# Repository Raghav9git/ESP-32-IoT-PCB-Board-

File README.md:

## ESP32-C3 IoT Sensor Development Board

A compact 4-layer IoT development board built around the ESP32-C3, integrating environmental sensing, local storage, USB-C power with LiPo battery management, and a programming/debug interface on a single board. Designed in KiCad 10.0.

This is a multi-domain hardware project that brings power electronics, mixed-signal sensor front-ends, digital interfaces, and RF-module integration together on one board — and routes them on a 4-layer stackup with dedicated power and ground planes.

## Overview

The goal of this board is a self-contained, battery-capable IoT platform: an ESP32-C3 (Wi-Fi + BLE) as the brain, surrounded by the supporting subsystems a real IoT device needs — clean regulated power, safe battery charging, local data storage, environmental sensors, and a robust USB programming path.

It was built as a deliberate skill-development project to practice end-to-end PCB design across several engineering domains in a single, non-trivial board, rather than a series of isolated single-function boards.

## Features

MCU: ESP32-C3-WROOM-02 module — Wi-Fi + Bluetooth LE
Power input: USB-C connector (power + data), with input fuse protection
Battery: LiPo battery connector with onboard charge management (MCP73871) and power-path control
Regulation: 3.3 V LDO (LM1117) for the logic rail, sourced from the 5 V USB rail
Programming/Debug: CP2102N USB-to-UART bridge with automatic boot/reset (DTR/RTS) circuit
Storage: microSD card slot (SPI) + onboard SPI flash (W25Q32)
Sensors:

BME280 — temperature, humidity, barometric pressure
TEMT6000 — ambient light
Electret microphone + MAX4466 pre-amplifier — audio/sound level

User interface: Boot and Reset buttons (with RC debounce), status LEDs, I²C OLED display header, GPIO breakout header
Debug: Test points on key SPI/SD signals
Protection: USB data-line ESD protection (USBLC6)
PCB: 4-layer design with dedicated power and ground planes

## Tech Specs

ItemDetailMicrocontrollerESP32-C3-WROOM-02 (Wi-Fi + BLE)PCB layers4 (signal / GND plane / power plane / signal)Power inputUSB-C (5 V) and LiPo batteryLogic rail3.3 V (LM1117 LDO)ChargingMCP73871 LiPo charger / power pathUSB–UART bridgeCP2102NStoragemicroSD (SPI) + W25Q32 SPI flashSensorsBME280, TEMT6000, MAX4466 mic ampInterfacesI²C, SPI, UART, GPIO headerDesign toolKiCad 10.0

## Subsystem Architecture

The board is organized as a set of interacting subsystems. Each block exists for a specific reason:

## Power & Battery Management

USB-C delivers 5 V, passed through a fuse for input protection. The MCP73871 handles LiPo charging and automatic power-path switching between USB power and battery, so the board runs from USB when connected and from battery otherwise. The LM1117 LDO derives the clean 3.3 V logic rail from the 5 V rail. Input and output decoupling capacitors sit close to the regulator for stability.

## MCU

The ESP32-C3-WROOM-02 is the core — a single-chip Wi-Fi + BLE module. It runs from the 3.3 V rail with local decoupling, and exposes the SPI, I²C, UART, and GPIO interfaces that connect to the rest of the board.

## Programming & Auto-Reset

A CP2102N USB-to-UART bridge provides the serial programming/debug interface over USB-C. The DTR/RTS auto-reset circuit (two transistors) automatically drives the EN and BOOT lines during flashing, so firmware can be uploaded without manually pressing buttons — the standard ESP programming convenience circuit. USBLC6 ESD protection guards the USB data lines.

## Storage

A microSD slot (SPI) provides removable local storage for data logging, and an onboard W25Q32 SPI flash offers fixed storage for configuration or firmware data. Test points on the SPI/SD lines allow probing during bring-up.

## Sensors (Mixed-Signal Front-Ends)

BME280 — digital environmental sensor (temperature, humidity, pressure) on the I²C/SPI bus.
TEMT6000 — analog ambient light sensor feeding an ADC input.
Electret mic + MAX4466 — an analog audio front-end; the MAX4466 amplifies the microphone signal to a usable level for the ADC.

The analog sensor front-ends are the mixed-signal portion of the design, where layout and grounding affect signal quality.

## User Interface

Boot and Reset buttons with RC debounce, status LEDs for power/operation indication, an I²C header for an OLED display, and a GPIO breakout header for expansion.

## Design Highlights

4-layer stackup with dedicated ground and power planes for clean power distribution and a solid low-impedance ground return — important on a board mixing RF, analog sensors, and digital interfaces.
Mixed-signal layout — separating noisy digital and switching activity from the analog sensor front-ends.
USB & ESD considerations — controlled USB data routing and dedicated ESD protection.
Net classes for differentiated trace widths (power vs. signal).
Test points on key debug nets for hardware bring-up.
Compact, thoughtful component placement following the power and signal flow.

## Project Status

~80% complete.

 Multi-page hierarchical schematic — complete, ERC passing
 Footprint assignment
 Component placement
 4-layer stackup and plane setup
 Routing (power and signal)
 Copper zones / ground pour
 Final silkscreen pass (labels, polarity marks, board info)
 Final DRC sign-off
 Manufacturing output (Gerbers / drill files)
 Fabrication and bring-up testing

Remaining work is finishing/polish: silkscreen cleanup, a final DRC pass, and generating manufacturing files.

## Skills Developed

This project was built to practice the full PCB workflow on a realistic, multi-domain board:

Multi-page hierarchical schematic design
Power electronics: LDO regulation, LiPo charge management, power-path design
Mixed-signal design: analog sensor front-ends alongside digital interfaces
RF module integration: ESP32-C3 placement and supporting circuitry
Digital interfaces: SPI (flash, SD), I²C (sensors, OLED), UART (programming)
USB & ESD: USB-C, USB-to-UART bridge, data-line protection
4-layer PCB layout: stackup, dedicated power/ground planes, copper zones
Net classes, trace-width selection, and DRC-driven debugging
Reading and applying datasheets for component configuration

## Tools

KiCad 10.0 — schematic capture and PCB layout
Component symbols, footprints, and 3D models sourced from KiCad libraries and standard component vendors

## References & Acknowledgments

This board was built as a learning project to develop hands-on PCB design skills across power, mixed-signal, and digital domains. The design follows and adapts a published KiCad IoT development-board reference/tutorial as a starting point, which I used to study how a complete, multi-subsystem board is architected, laid out on four layers, and prepared for manufacturing.

License

Released under the MIT License. See LICENSE for details.

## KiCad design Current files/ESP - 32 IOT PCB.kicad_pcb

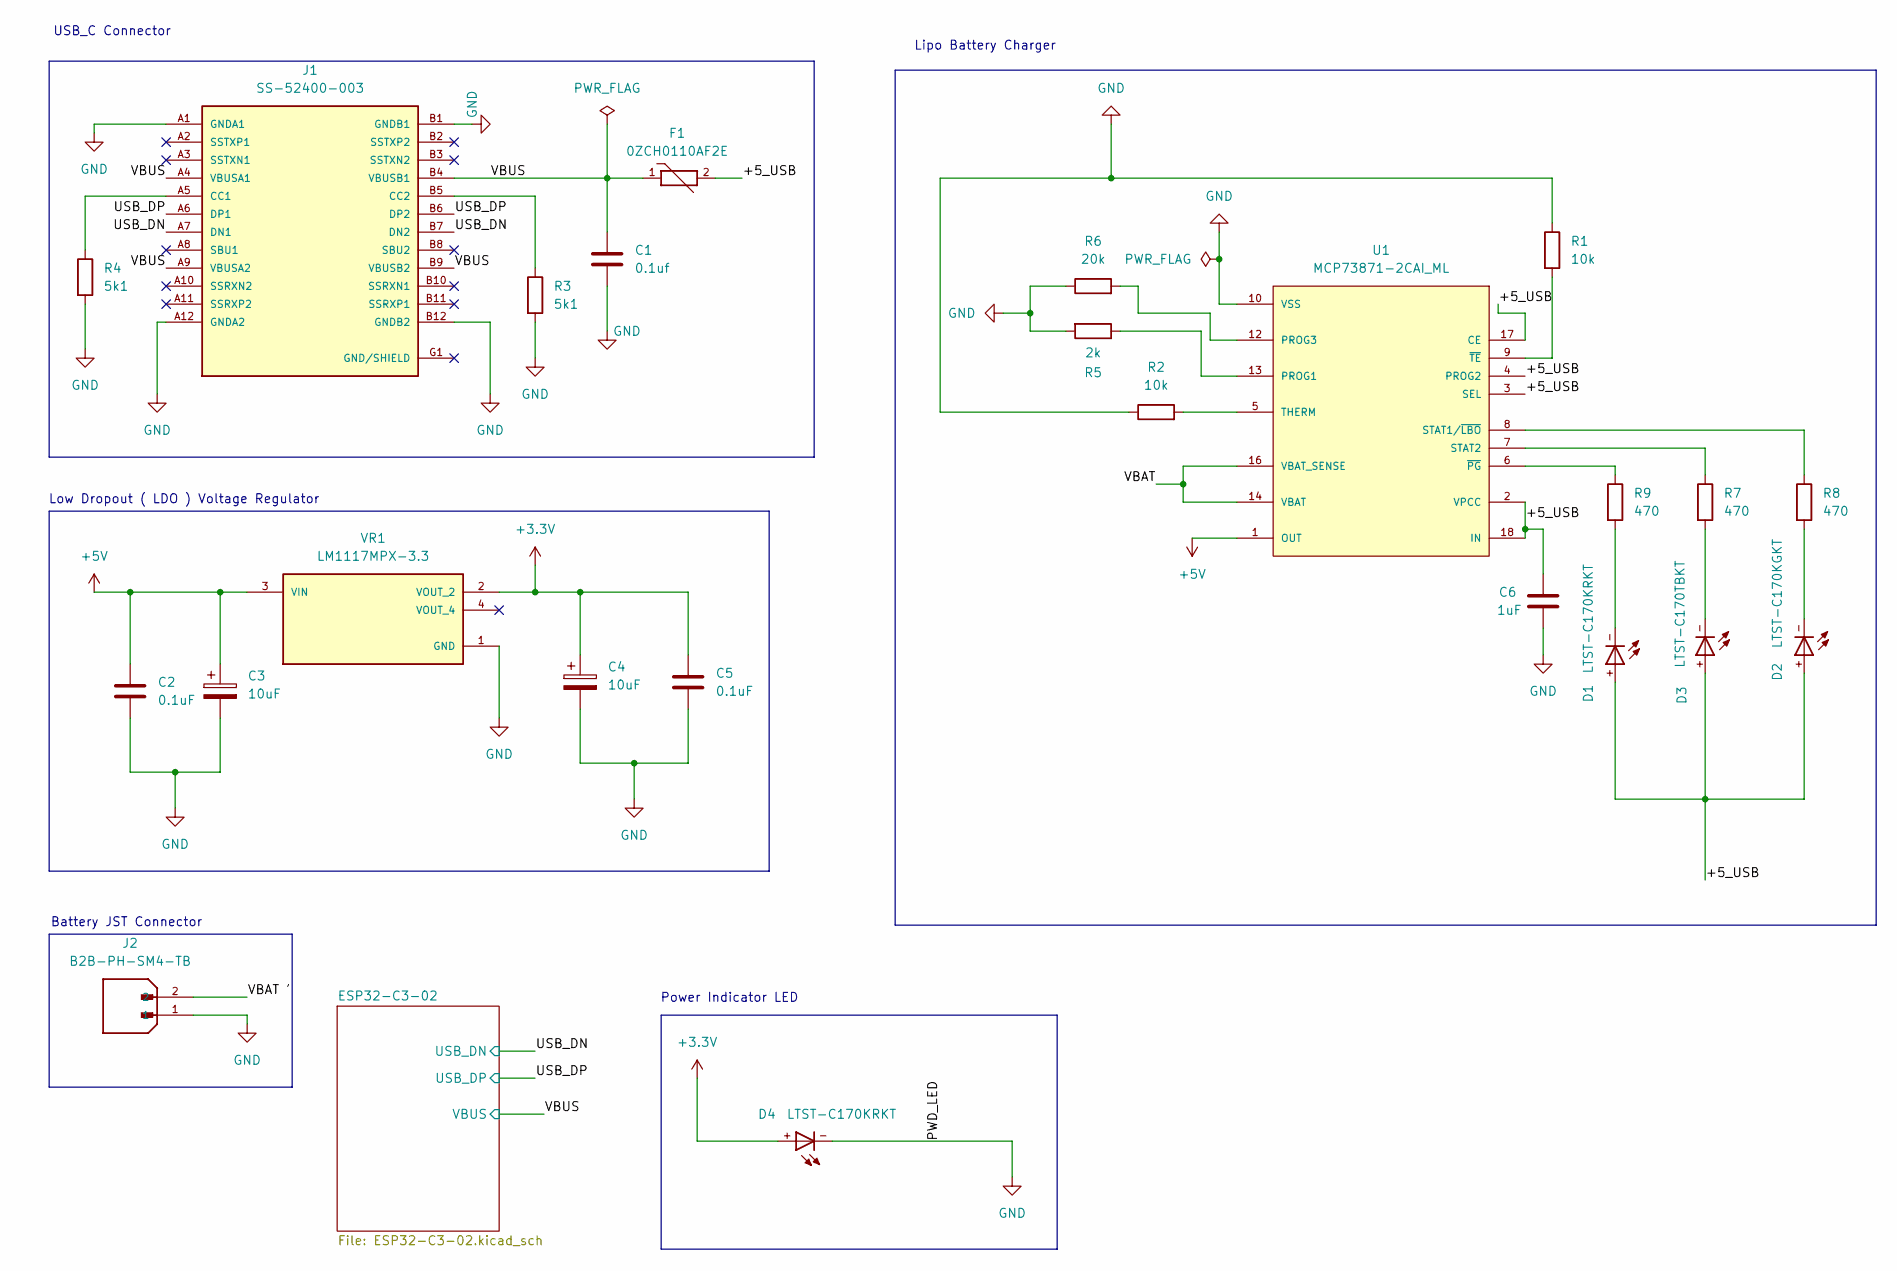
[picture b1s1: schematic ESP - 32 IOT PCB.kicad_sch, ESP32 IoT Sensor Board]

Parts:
C1: 0.1uf; C_0805_2012Metric
C2, C5: 0.1uF; C_0805_2012Metric
C3, C4: 10uF; CP_EIA-3216-18_Kemet-A
C6: 1uF; C_0805_2012Metric
D1, D4: LTST-C170KRKT; DIOC200X125X110
D2: LTST-C170KGKT; DIOC200X125X110
D3: LTST-C170TBKT; DIOC200X125X110
F1: 0ZCH0110AF2E; FUSC3225X100N; PARTREV Apr2023
J1: SS-52400-003; BELFUSE_SS-52400-003; PARTREV A0
J2: B2B-PH-SM4-TB; JST_B2B-PH-SM4-TB; PARTREV N/A
R1, R2: 10k; R_0805_2012Metric
R3, R4: 5k1; R_0805_2012Metric
R5: 2k; R_0805_2012Metric
R6: 20k; R_0805_2012Metric
R7, R8, R9: 470; R_0805_2012Metric
U1: MCP73871-2CAI_ML; QFN50P400X400X100-21N; PARTREV D
VR1: LM1117MPX-3.3; VREG_LM1117MPX-3.3; PARTREV O

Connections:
+3.3V: C4.1, C5.1, D4.+, VR1.2 (VOUT_2); also elsewhere on the board
+5V: C2.1, C3.1, U1.1 (OUT), U1.20 (OUT), VR1.3 (VIN)
/+5_USB: C6.1, D1.+, D2.+, D3.+, F1.2, U1.2 (VPCC), U1.3 (SEL), U1.4 (PROG2), U1.17 (CE), U1.18 (IN), U1.19 (IN)
/USB_DN: J1.A7 (DN1), J1.B7 (DN2); also elsewhere on the board
/USB_DP: J1.A6 (DP1), J1.B6 (DP2); also elsewhere on the board
/VBAT: U1.14 (VBAT), U1.15 (VBAT), U1.16 (VBAT_SENSE)
/VBAT ': J2.2
/VBUS: C1.1, F1.1, J1.A4 (VBUSA1), J1.A9 (VBUSA2), J1.B4 (VBUSB1), J1.B9 (VBUSB2); also elsewhere on the board
GND: C1.2, C2.2, C3.2, C4.2, C5.2, C6.2, D4.-, J1.A1 (GNDA1), J1.A12 (GNDA2), J1.B1 (GNDB1), J1.B12 (GNDB2), J2.1, R1.1, R2.1, R3.2, R4.2, R5.2, R6.1, U1.10 (VSS), U1.11 (VSS), U1.21 (VSS), VR1.1 (GND); also elsewhere on the board
unnamed: D1.-, R9.2
unnamed: D2.-, R8.2
unnamed: D3.-, R7.2
unnamed: J1.A5 (CC1), R4.1
unnamed: J1.B5 (CC2), R3.1
unnamed: R5.1, U1.13 (PROG1)
unnamed: R6.2, U1.12 (PROG3)
unnamed: R8.1, U1.8 (STAT1/~LBO)
unnamed: R7.1, U1.7 (STAT2)
unnamed: R2.2, U1.5 (THERM)
unnamed: R9.1, U1.6 (~PG)
unnamed: R1.2, U1.9 (~TE)

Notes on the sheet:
Lipo Battery Charger
Power Indicator LED
USB_C Connector
Battery JST Connector
Low Dropout ( LDO ) Voltage Regulator

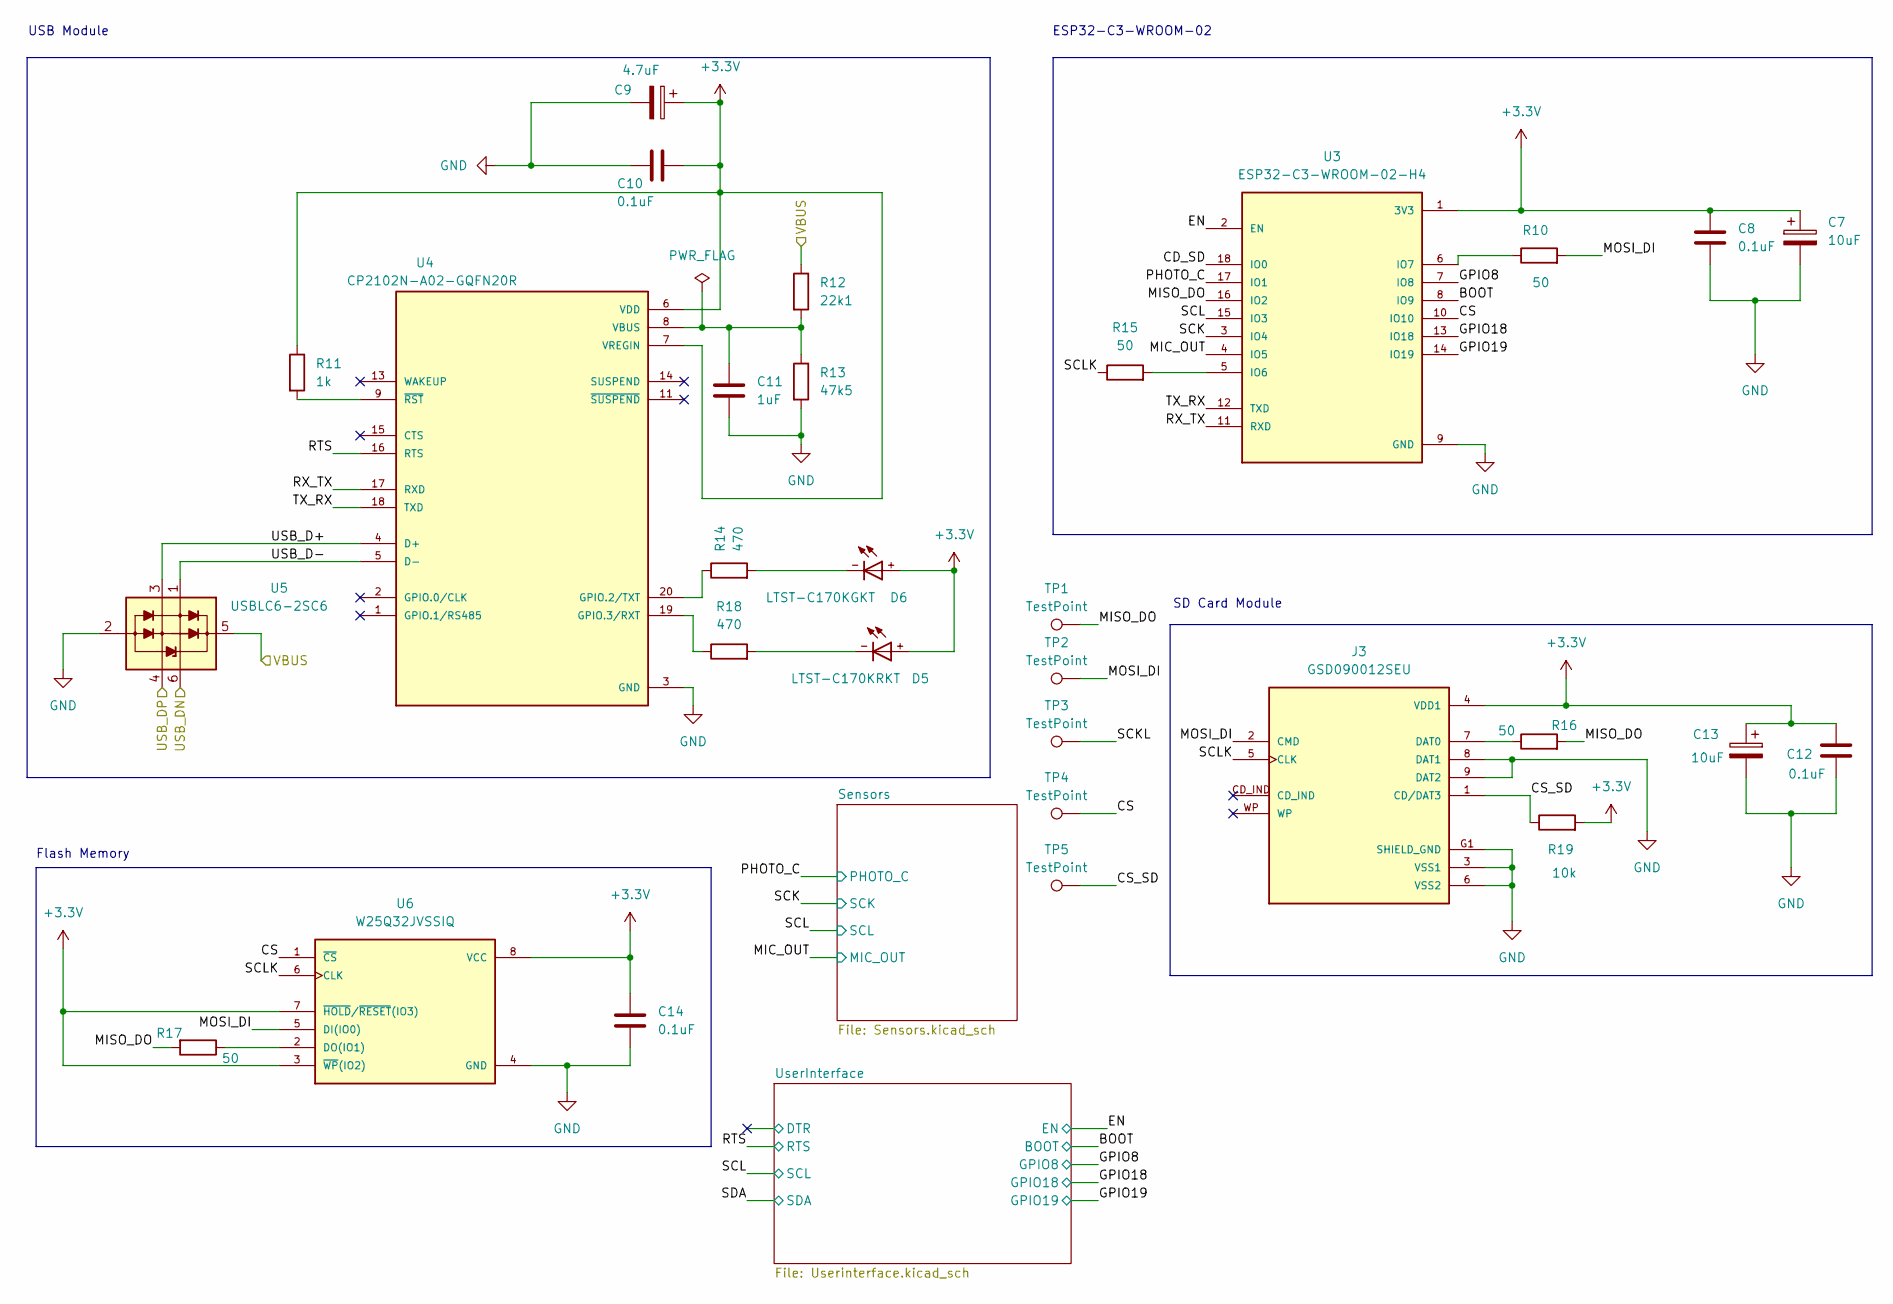
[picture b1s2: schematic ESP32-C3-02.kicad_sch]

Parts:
C7, C13: 10uF; CP_EIA-3216-18_Kemet-A
C8, C10, C12, C14: 0.1uF; C_0805_2012Metric
C9: 4.7uF; CP_EIA-3216-18_Kemet-A
C11: 1uF; C_0805_2012Metric
D5: LTST-C170KRKT; DIOC200X125X110
D6: LTST-C170KGKT; DIOC200X125X110
J3: GSD090012SEU; AMPHENOL_GSD090012SEU; PARTREV E
R10, R15, R16, R17: 50; R_0805_2012Metric
R11: 1k; R_0805_2012Metric
R12: 22k1; R_0805_2012Metric
R13: 47k5; R_0805_2012Metric
R14, R18: 470; R_0805_2012Metric
R19: 10k; R_0805_2012Metric
TP1, TP2, TP3, TP4, TP5: TestPoint; TestPoint_Pad_D1.0mm
U3: ESP32-C3-WROOM-02-H4; MODULE_ESP32-C3-WROOM-02-H4
U4: CP2102N-A02-GQFN20R; SILABS_CP2102N-A02-GQFN20R; PARTREV 1.3
U5: USBLC6-2SC6; SOT-23-6
U6: W25Q32JVSSIQ; SOIC127P790X216-8N; M_PART_NUMBER W25QXX

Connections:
+3.3V: C7.1, C8.1, C9.1, C10.2, C12.1, C13.1, C14.1, D5.+, D6.+, J3.4 (VDD1), R11.1, R19.2, U3.1 (3V3), U4.6 (VDD), U4.7 (VREGIN), U6.3 (~WP(IO2)), U6.7 (~HOLD/~RESET(IO3)), U6.8 (VCC); also elsewhere on the board
/ESP32-C3-02/BOOT: U3.8 (IO9); also elsewhere on the board
/ESP32-C3-02/CD_SD: U3.18 (IO0)
/ESP32-C3-02/CS: TP4.1, U3.10 (IO10), U6.1 (~CS)
/ESP32-C3-02/CS_SD: J3.1 (CD/DAT3), R19.1, TP5.1
/ESP32-C3-02/EN: U3.2 (EN); also elsewhere on the board
/ESP32-C3-02/GPIO8: U3.7 (IO8); also elsewhere on the board
/ESP32-C3-02/GPIO18: U3.13 (IO18); also elsewhere on the board
/ESP32-C3-02/GPIO19: U3.14 (IO19); also elsewhere on the board
/ESP32-C3-02/MIC_OUT: U3.4 (IO5); also elsewhere on the board
/ESP32-C3-02/MISO_DO: R16.2, R17.2, TP1.1, U3.16 (IO2)
/ESP32-C3-02/MOSI_DI: J3.2 (CMD), R10.2, TP2.1, U6.5 (DI(IO0))
/ESP32-C3-02/PHOTO_C: U3.17 (IO1); also elsewhere on the board
/ESP32-C3-02/RTS: U4.16 (RTS); also elsewhere on the board
/ESP32-C3-02/RX_TX: U3.11 (RXD), U4.17 (RXD)
/ESP32-C3-02/SCK: U3.3 (IO4); also elsewhere on the board
/ESP32-C3-02/SCL: U3.15 (IO3); also elsewhere on the board
/ESP32-C3-02/SCLK: J3.5 (CLK), R15.1, U6.6 (CLK)
/ESP32-C3-02/TX_RX: U3.12 (TXD), U4.18 (TXD)
/ESP32-C3-02/USB_D+: U4.4 (D+), U5.3 (L2)
/ESP32-C3-02/USB_D-: U4.5 (D-), U5.1 (L1)
/USB_DN: U5.6 (L1); also elsewhere on the board
/USB_DP: U5.4 (L2); also elsewhere on the board
/VBUS: R12.1, U5.5 (VP); also elsewhere on the board
GND: C7.2, C8.2, C9.2, C10.1, C11.2, C12.2, C13.2, C14.2, J3.3 (VSS1), J3.6 (VSS2), J3.8 (DAT1), J3.9 (DAT2), J3.G1 (SHIELD_GND), J3.G2 (SHIELD_GND), J3.G3 (SHIELD_GND), J3.G4 (SHIELD_GND), R13.2, U3.9 (GND), U3.19 (GND), U3.20 (GND), U3.21 (GND), U3.22 (GND), U3.23 (GND), U3.24 (GND), U3.25 (GND), U3.26 (GND), U3.27 (GND), U3.28 (GND), U3.29 (GND), U3.30 (GND), U3.31 (GND), U3.32 (GND), U3.33 (GND), U3.34 (GND), U3.35 (GND), U3.36 (GND), U3.37 (GND), U3.38 (GND), U3.39 (GND), U4.3 (GND), U4.12 (GND), U4.21 (GND), U5.2 (VN), U6.4 (GND); also elsewhere on the board
unnamed: D5.-, R18.2
unnamed: D6.-, R14.2
unnamed: J3.7 (DAT0), R16.1
unnamed: R15.2, U3.5 (IO6)
unnamed: R10.1, U3.6 (IO7)
unnamed: R14.1, U4.20 (GPIO.2/TXT)
unnamed: R18.1, U4.19 (GPIO.3/RXT)
unnamed: C11.1, R12.2, R13.1, U4.8 (VBUS)
unnamed: R11.2, U4.9 (~RST)
unnamed: R17.1, U6.2 (DO(IO1))

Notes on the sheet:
USB Module
Flash Memory
ESP32-C3-WROOM-02
SD Card Module

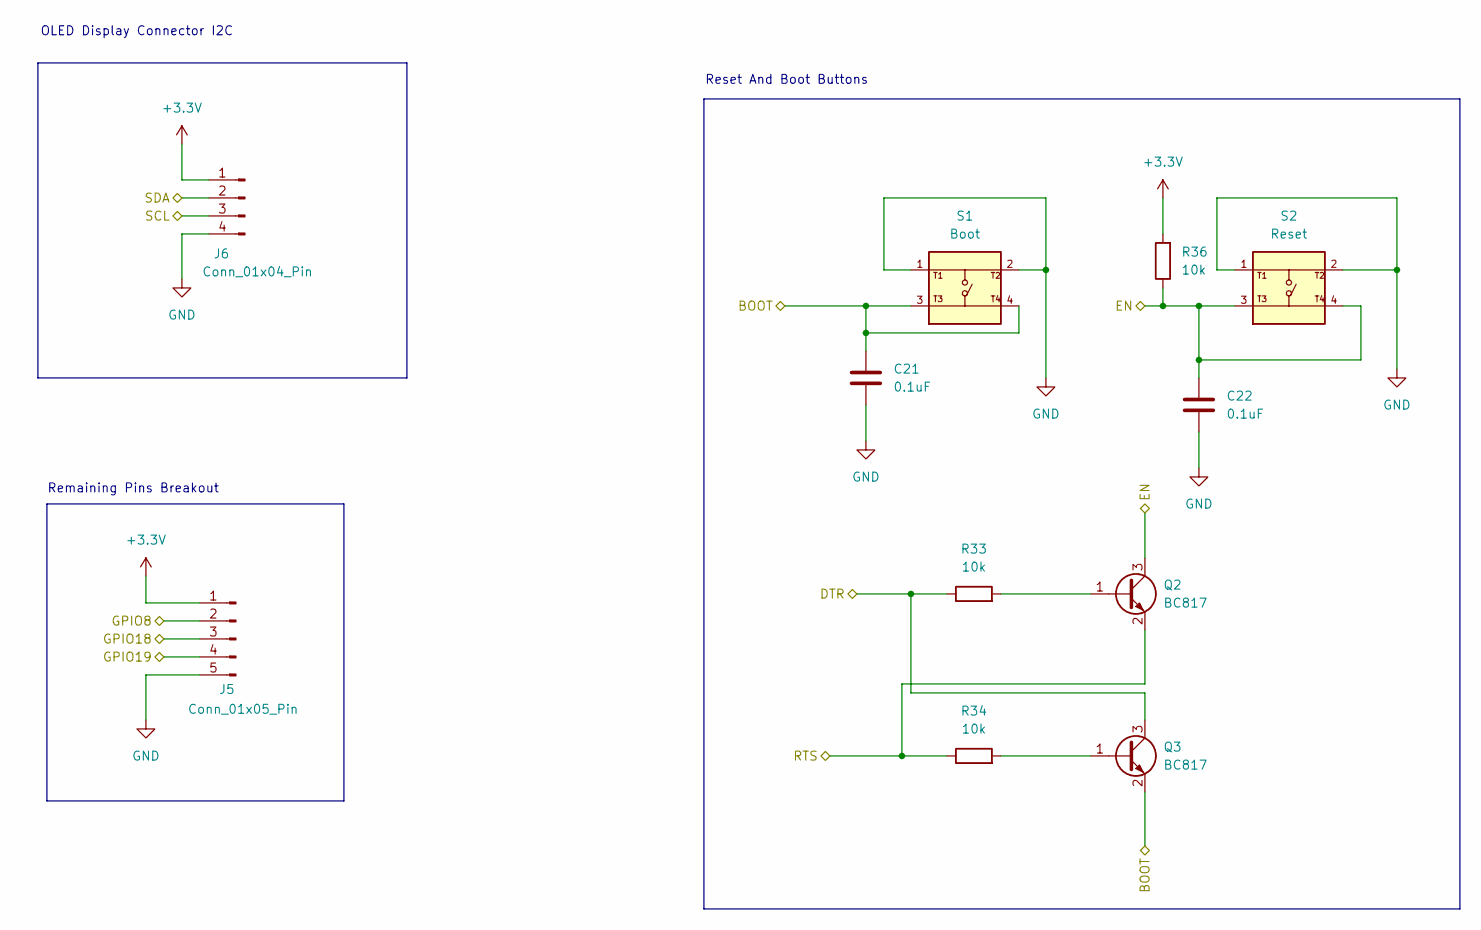
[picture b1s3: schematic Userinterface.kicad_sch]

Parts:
C21, C22: 0.1uF; C_0805_2012Metric
J5: Conn_01x05_Pin; PinHeader_1x05_P2.54mm_Vertical
J6: Conn_01x04_Pin; PinHeader_1x05_P2.54mm_Vertical
Q2, Q3: BC817; SOT-23
R33, R34, R36: 10k; R_0805_2012Metric
S1: Boot; SW_USLPT2819DT2TR; PARTREV P
S2: Reset; SW_USLPT2819DT2TR; PARTREV P

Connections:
+3.3V: J5.1, J6.1, R36.2; also elsewhere on the board
/ESP32-C3-02/BOOT: C21.1, Q3.2 (E), S1.3, S1.4; also elsewhere on the board
/ESP32-C3-02/EN: C22.1, Q2.3 (C), R36.1, S2.3, S2.4; also elsewhere on the board
/ESP32-C3-02/GPIO8: J5.2; also elsewhere on the board
/ESP32-C3-02/GPIO18: J5.3; also elsewhere on the board
/ESP32-C3-02/GPIO19: J5.4; also elsewhere on the board
/ESP32-C3-02/RTS: Q2.2 (E), R34.1; also elsewhere on the board
/ESP32-C3-02/SCL: J6.3; also elsewhere on the board
/ESP32-C3-02/SDA: J6.2
/ESP32-C3-02/UserInterface/DTR: Q3.3 (C), R33.1
GND: C21.2, C22.2, J5.5, J6.4, S1.1, S1.2, S2.1, S2.2; also elsewhere on the board
unnamed: Q2.1 (B), R33.2
unnamed: Q3.1 (B), R34.2

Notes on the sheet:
OLED Display Connector I2C
Reset And Boot Buttons
Remaining Pins Breakout

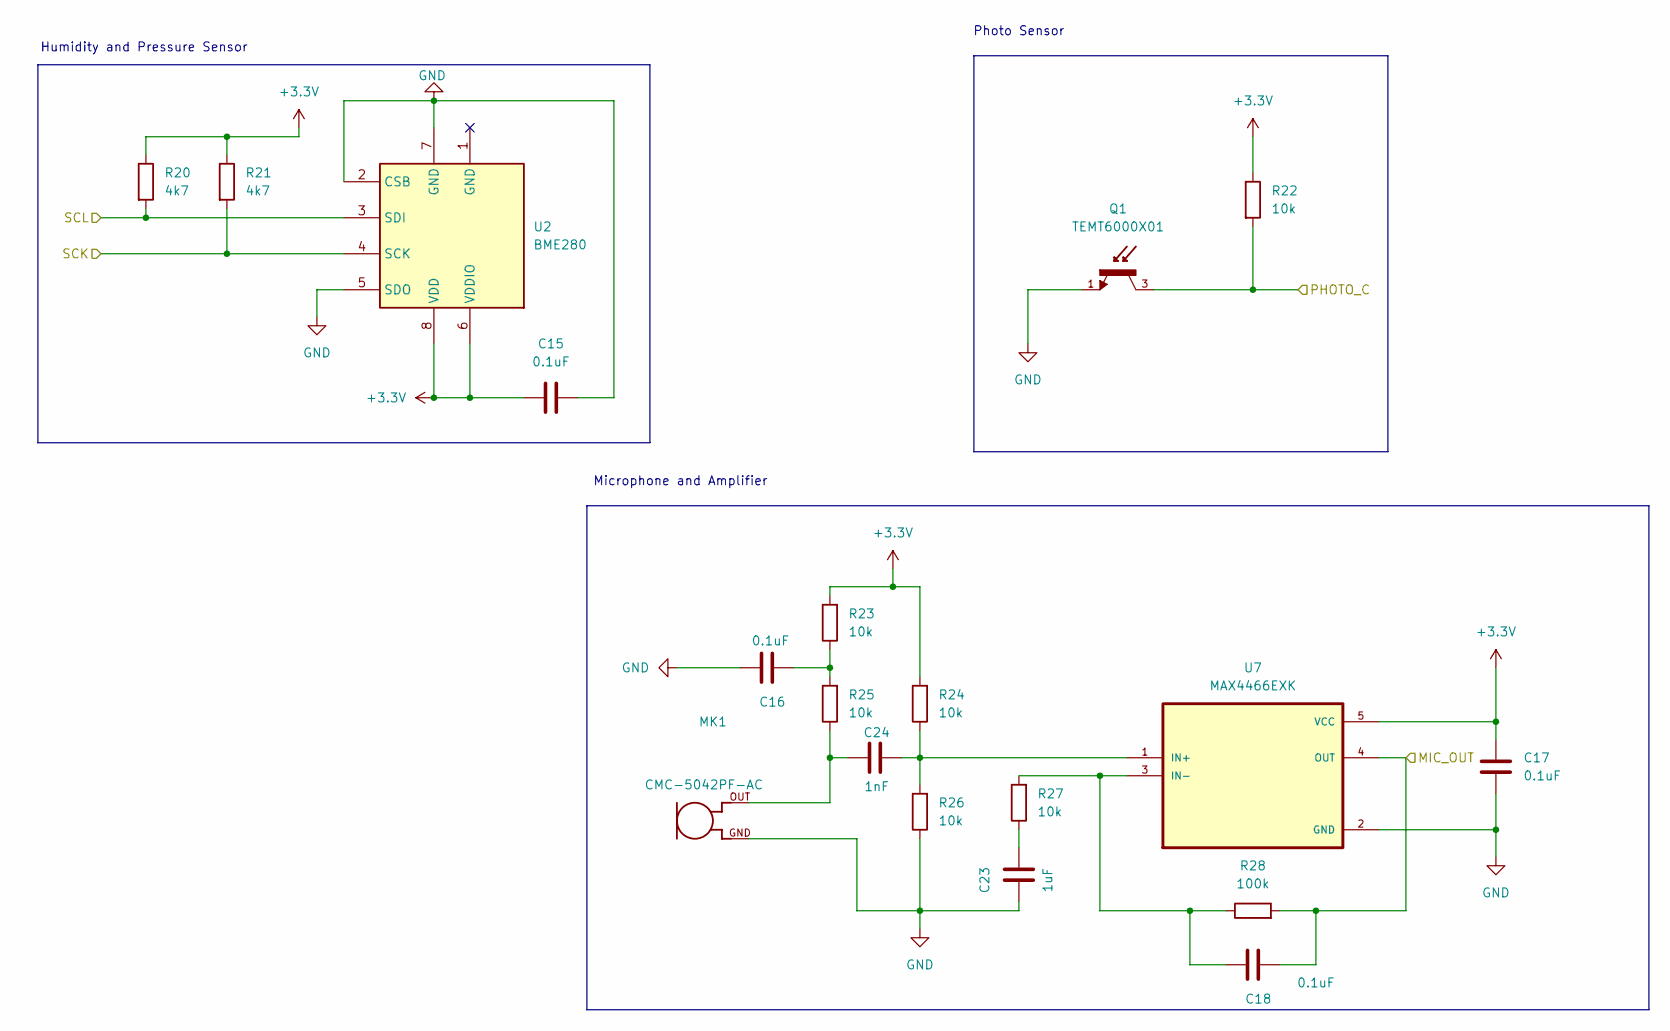
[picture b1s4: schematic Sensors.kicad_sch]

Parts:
C15, C16, C17, C18: 0.1uF; C_0805_2012Metric
C23: 1uF; C_0805_2012Metric
C24: 1nF; C_0805_2012Metric
MK1: CMC-5042PF-AC; CUI_CMC-5042PF-AC
Q1: TEMT6000X01; TRANS_TEMT6000X01; PARTREV 1.9
R20, R21: 4k7; R_0805_2012Metric
R22, R23, R24, R25, R26, R27: 10k; R_0805_2012Metric
R28: 100k; R_0805_2012Metric
U2: BME280; Bosch_LGA-8_2.5x2.5mm_P0.65mm_ClockwisePinNumbering
U7: MAX4466EXK; SOT65P210X110-5N

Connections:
+3.3V: C15.1, C17.1, R20.1, R21.1, R22.1, R23.2, R24.2, U2.6 (VDDIO), U2.8 (VDD), U7.5 (VCC); also elsewhere on the board
/ESP32-C3-02/MIC_OUT: C18.2, R28.2, U7.4 (OUT); also elsewhere on the board
/ESP32-C3-02/PHOTO_C: Q1.3, R22.2; also elsewhere on the board
/ESP32-C3-02/SCK: R21.2, U2.4 (SCK); also elsewhere on the board
/ESP32-C3-02/SCL: R20.2, U2.3 (SDI); also elsewhere on the board
GND: C15.2, C16.1, C17.2, C23.2, MK1.GND, Q1.1, R26.1, U2.2 (CSB), U2.5 (SDO), U2.7 (GND), U7.2 (GND); also elsewhere on the board
unnamed: C16.2, R23.1, R25.2
unnamed: C23.1, R27.1
unnamed: C24.1, MK1.OUT, R25.1
unnamed: C24.2, R24.1, R26.2, U7.1 (IN+)
unnamed: C18.1, R27.2, R28.1, U7.3 (IN-)

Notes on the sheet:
Photo Sensor
Microphone and Amplifier
Humidity and Pressure Sensor

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
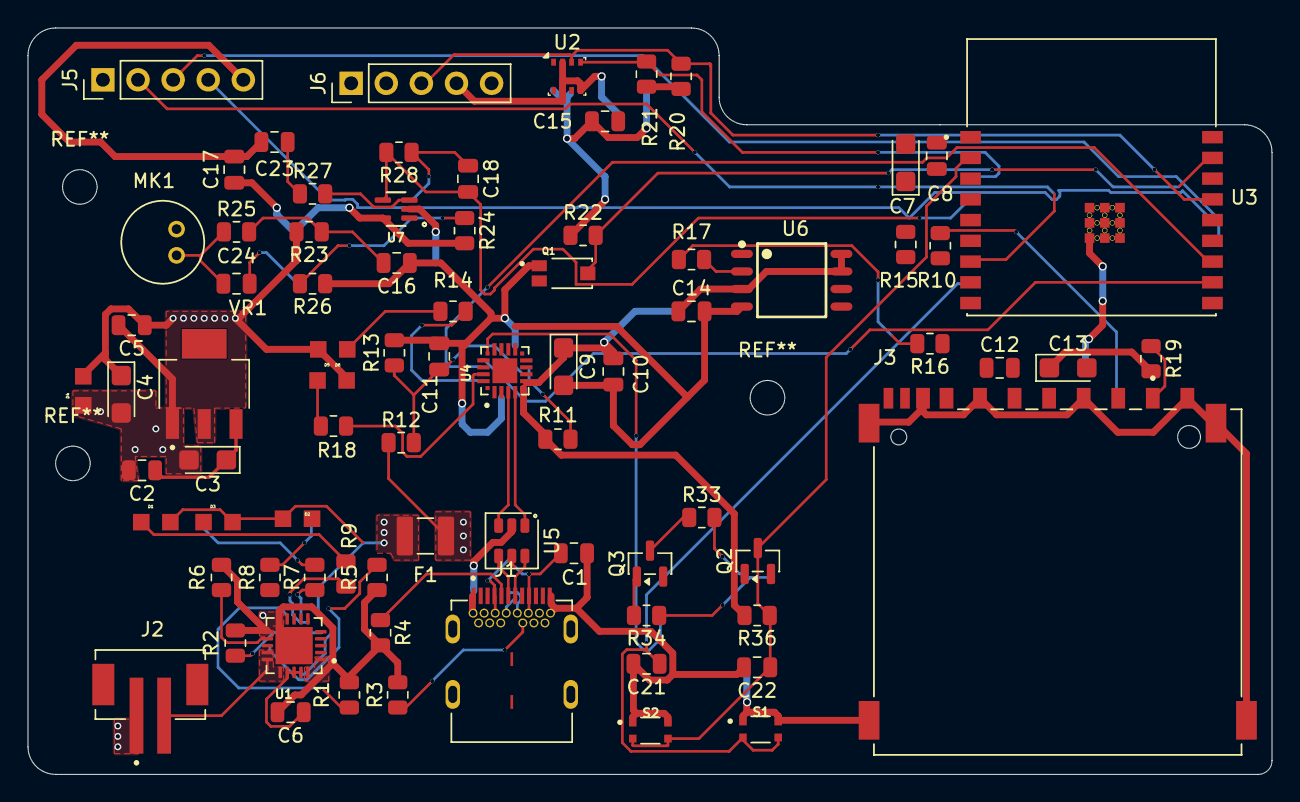
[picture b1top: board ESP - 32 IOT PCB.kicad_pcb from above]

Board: 4 copper layers, 90.0 x 54.0 mm, 79 parts (0 on the bottom side), 57 nets.

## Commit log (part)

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2026-06-16 Rename Screenshot 2026-06-16 143926.png to 3D view
2026-06-19 Rename 3D view to 3D view.png
2026-06-19 Rename Screenshot 2026-06-16 144022.png to PCB layout.png
2026-06-19 Rename Screenshot 2026-06-16 144109.png to Power Circuitry.png
2026-06-19 Rename Screenshot 2026-06-16 144355.png to Type C USB.png
2026-06-19 Rename Screenshot 2026-06-16 144411.png to ESP-32 Module.png
2026-06-19 Rename Screenshot 2026-06-16 144436.png to SD Card Module.png
2026-06-19 Rename Screenshot 2026-06-16 144452.png to Memory & Hierarchical Sheets.png
2026-06-19 Rename Screenshot 2026-06-16 144512.png to Sensors.png
2026-06-19 Rename Screenshot 2026-06-16 144535.png to User Interface.png
